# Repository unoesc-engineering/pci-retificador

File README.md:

# Retificador em placa de circuito impresso

Este projeto tem como propósito a elaboração de
um protótipo de retificador, a fim de tomar conhecimento da
interação entre componentes com os conhecimentos da
engenharia, principalmente nas disciplinas de eletrônica
analógica, além de conteúdos adjacentes adquiridos no decorrer
do curso até o presente. Os retificadores são responsáveis por
converter uma tensão em corrente alternada para tensão em
corrente contínua. São muito utilizados no cotidiano já que
fazem essa transformação CA-CC, estão presente em eletrônicos
ligados a tomada, já que sua fonte de alimentação fornece
corrente alternada e os equipamentos precisam de corrente
contínua para funcionarem adequadamente. Dessa forma
desenvolvemos um projeto de retificador em que o equipamento
no qual ele será acoplado necessita de baixa potência e alta
confiabilidade.

## Contribuidores

 - Bruna Stofel
 - Bruno Cesca
 - Mateus Calza

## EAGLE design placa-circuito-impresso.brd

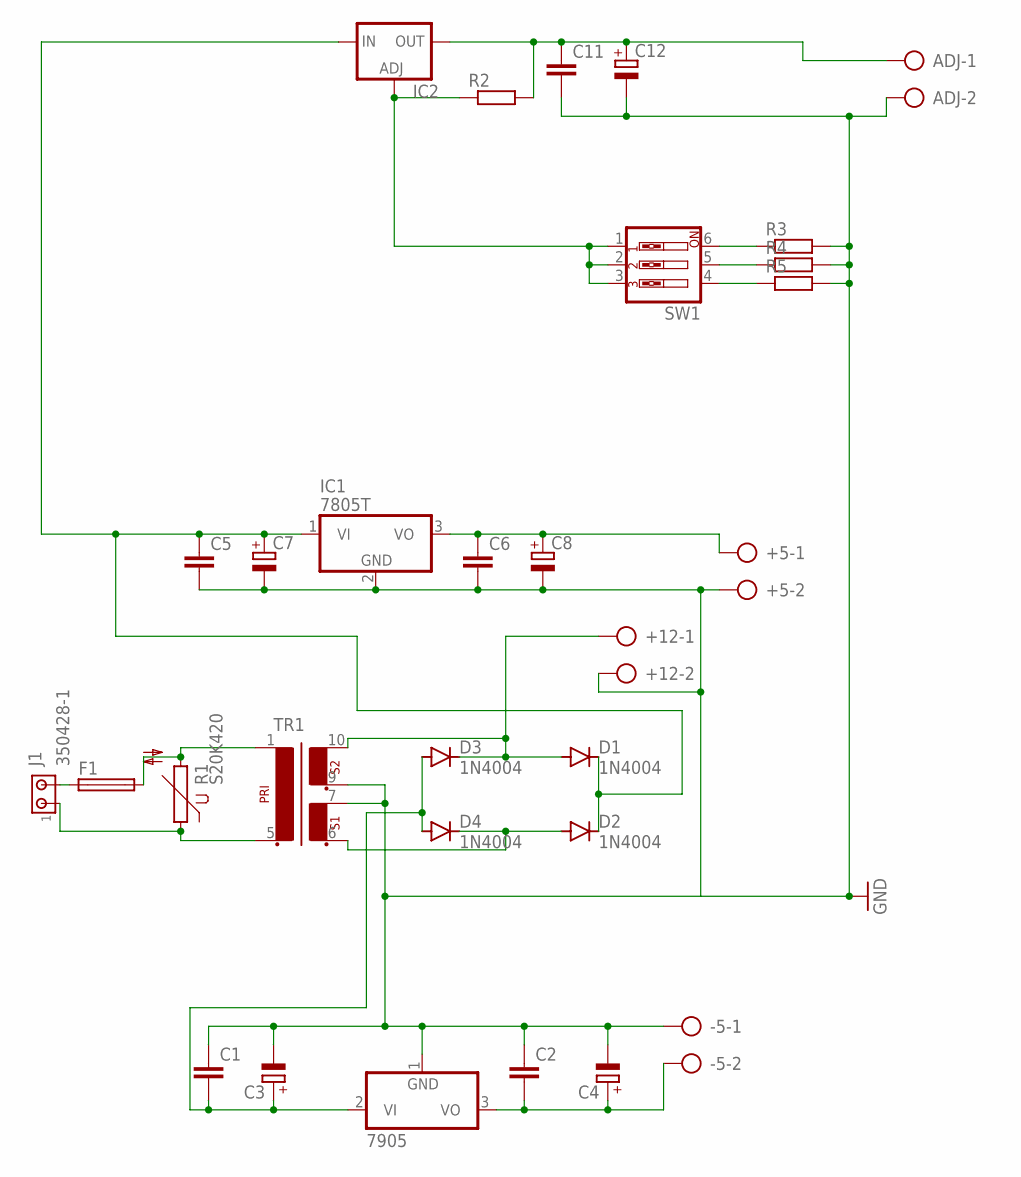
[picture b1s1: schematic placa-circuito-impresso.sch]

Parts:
7905: 7905T; TO220H
+5, +12: AK500/2-H
-5: AK500/2-H
ADJ: AK500/2-H
C1, C2, C5, C6, C11: C-EU025-025X050; C025-025X050
C3, C4, C7, C8, C12: CPOL-EUE2,5-6E; E2,5-6E
D1, D2, D3, D4: 1N4004; DO41-10
F1: GSH15
IC1: 7805T; TO220H
IC2: LM317TL; 317TL
J1: 350428-1
R1: S20K420
R2, R3, R4, R5: R-EU_0204/7; 0204/7
SW1: SW_DIP-3; EDG-03
TR1: EI30-2

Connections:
GND: 7905.1 (GND), +5.2, +12.2, -5.1, ADJ.2, C1.1, C2.1, C3.-, C4.-, C5.2, C6.2, C7.-, C8.-, C11.2, C12.-, IC1.2 (GND), R3.2, R4.2, R5.2, TR1.7 (4), TR1.9 (5)
unnamed: F1.1, J1.2
unnamed: J1.1, R1.1, TR1.5 (2)
unnamed: F1.2, R1.2, TR1.1
unnamed: +12.1, D1.A, D3.C, TR1.10 (6)
unnamed: R3.1, SW1.6
unnamed: 7905.2 (VI), C1.2, C3.+, D3.A, D4.A
unnamed: R4.1, SW1.5
unnamed: 7905.3 (VO), -5.2, C2.2, C4.+
unnamed: +5.1, C6.1, C8.+, IC1.3 (VO)
unnamed: C5.1, C7.+, D1.C, D2.C, IC1.1 (VI), IC2.3 (IN)
unnamed: ADJ.1, C11.1, C12.+, IC2.2 (OUT), R2.2
unnamed: D2.A, D4.C, TR1.6 (3)
unnamed: IC2.1 (ADJ), R2.1, SW1.1, SW1.2, SW1.3
unnamed: R5.1, SW1.4

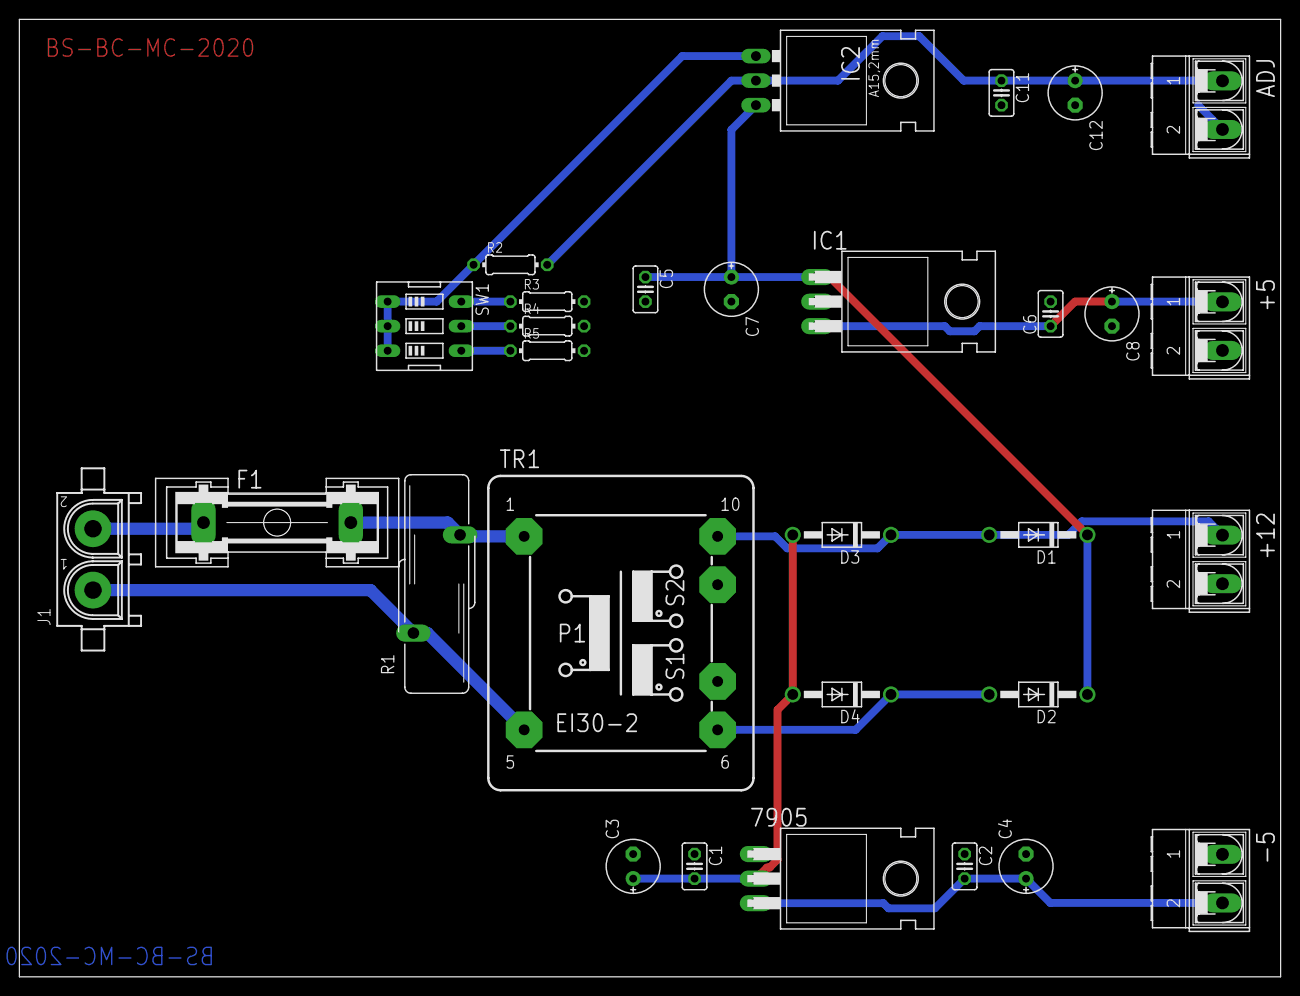
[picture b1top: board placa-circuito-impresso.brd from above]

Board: 2 copper layers, 130.5 x 99.1 mm, 30 parts (0 on the bottom side), 15 nets.

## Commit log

2020-09-28 Iniciando
2020-09-28 Atualizando espessura das linhas e reorganizando
2020-09-28 Linhas automáticas
2020-09-28 Atualizações na board
2020-09-28 Reposicionando na board
2020-09-28 Ajustes na board
2020-09-28 Malha de GND e impressões.
2020-09-28 Reorganizando projeto.
2020-09-28 PCI no relatório
2020-09-28 Conclusão e referências.
2020-09-28 Atualização no relatório
